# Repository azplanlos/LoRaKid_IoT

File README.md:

# LoRaKid

This is an IOT project to create hard and software for a kid's mobile phone like device but operation on LoRaWan over TTN.

CURRENTLY THIS IS WORK IN PROGRESS

## Image creation

Bitmaps can be created here: https://javl.github.io/image2cpp/

Settings are:

-

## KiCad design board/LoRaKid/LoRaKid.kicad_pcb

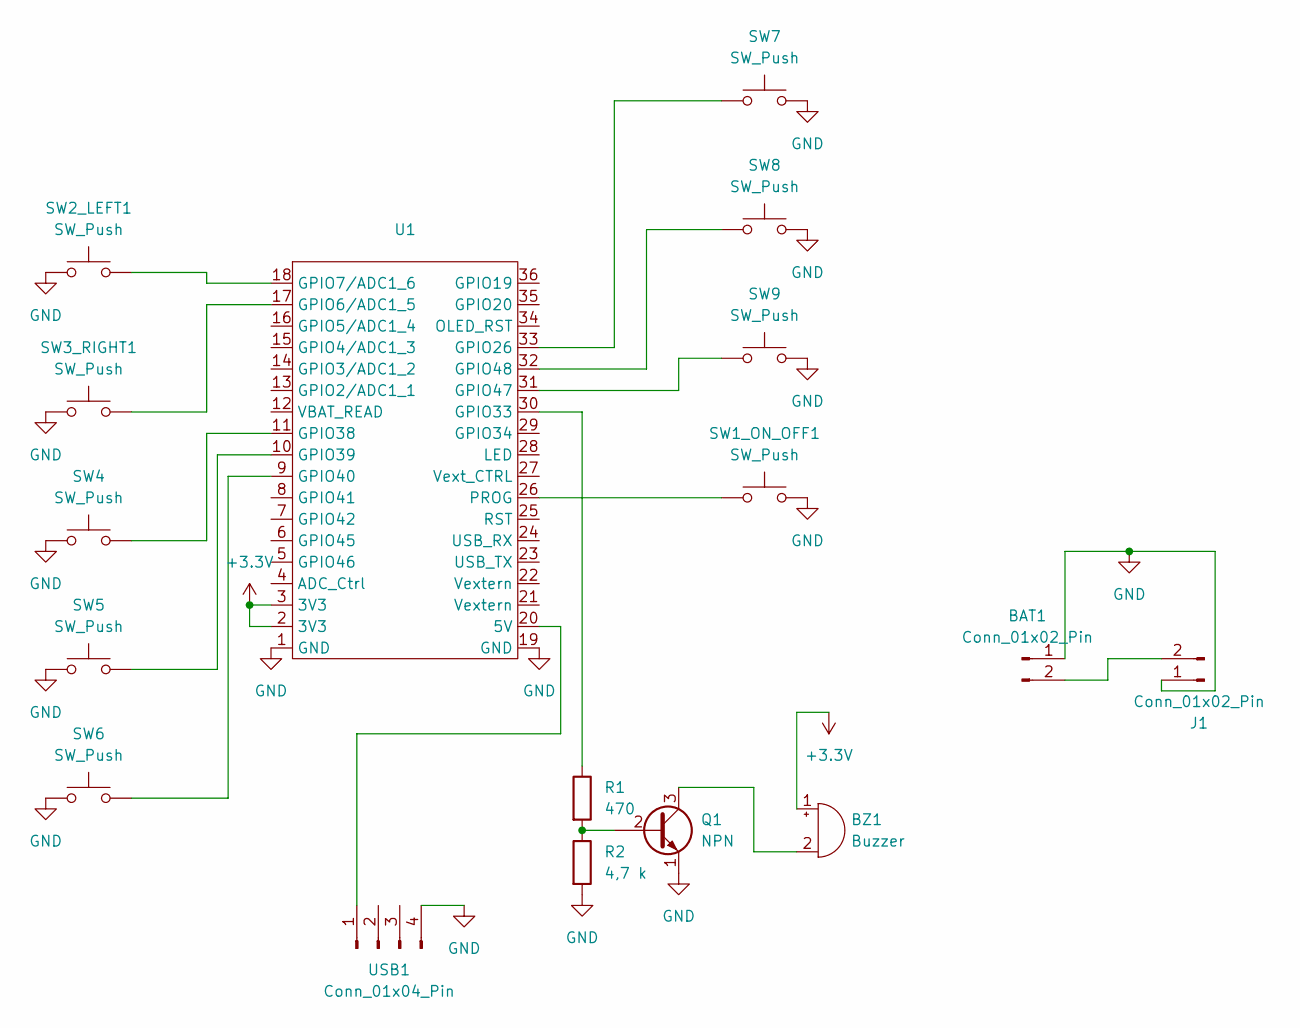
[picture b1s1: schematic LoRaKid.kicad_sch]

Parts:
BAT1: Conn_01x02_Pin; JST_PH_B2B-PH-K_1x02_P2.00mm_Vertical
BZ1: Buzzer; Buzzer_12x9.5RM7.6
J1: Conn_01x02_Pin; PinHeader_1x02_P2.54mm_Vertical
Q1: NPN; TO-92_Inline
R1: 470; R_0805_2012Metric_Pad1.20x1.40mm_HandSolder
R2: 4,7 k; R_0805_2012Metric_Pad1.20x1.40mm_HandSolder
SW1_ON_OFF1, SW2_LEFT1, SW3_RIGHT1, SW4, SW5, SW6, SW7, SW8, SW9: SW_Push; SW_SPST_Omron_B3FS-100xP
U1: Heltec LoRa 32 V3
USB1: Conn_01x04_Pin; PinSocket_1x04_P2.54mm_Vertical

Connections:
+3.3V: BZ1.1 (+), U1.2 (3V3), U1.3 (3V3)
GND: BAT1.1, J1.1, Q1.1 (E), R2.2, SW1_ON_OFF1.2, SW2_LEFT1.1, SW3_RIGHT1.1, SW4.1, SW5.1, SW6.1, SW7.2, SW8.2, SW9.2, U1.1 (GND), U1.19 (GND), USB1.4
unnamed: BAT1.2, J1.2
unnamed: BZ1.2 (-), Q1.3 (C)
unnamed: Q1.2 (B), R1.2, R2.1
unnamed: U1.20 (5V), USB1.1
unnamed: SW3_RIGHT1.2, U1.17 (GPIO6/ADC1_5)
unnamed: SW2_LEFT1.2, U1.18 (GPIO7/ADC1_6)
unnamed: SW7.1, U1.33 (GPIO26)
unnamed: R1.1, U1.30 (GPIO33)
unnamed: SW4.2, U1.11 (GPIO38)
unnamed: SW5.2, U1.10 (GPIO39)
unnamed: SW6.2, U1.9 (GPIO40)
unnamed: SW9.1, U1.31 (GPIO47)
unnamed: SW8.1, U1.32 (GPIO48)
unnamed: SW1_ON_OFF1.1, U1.26 (PROG)

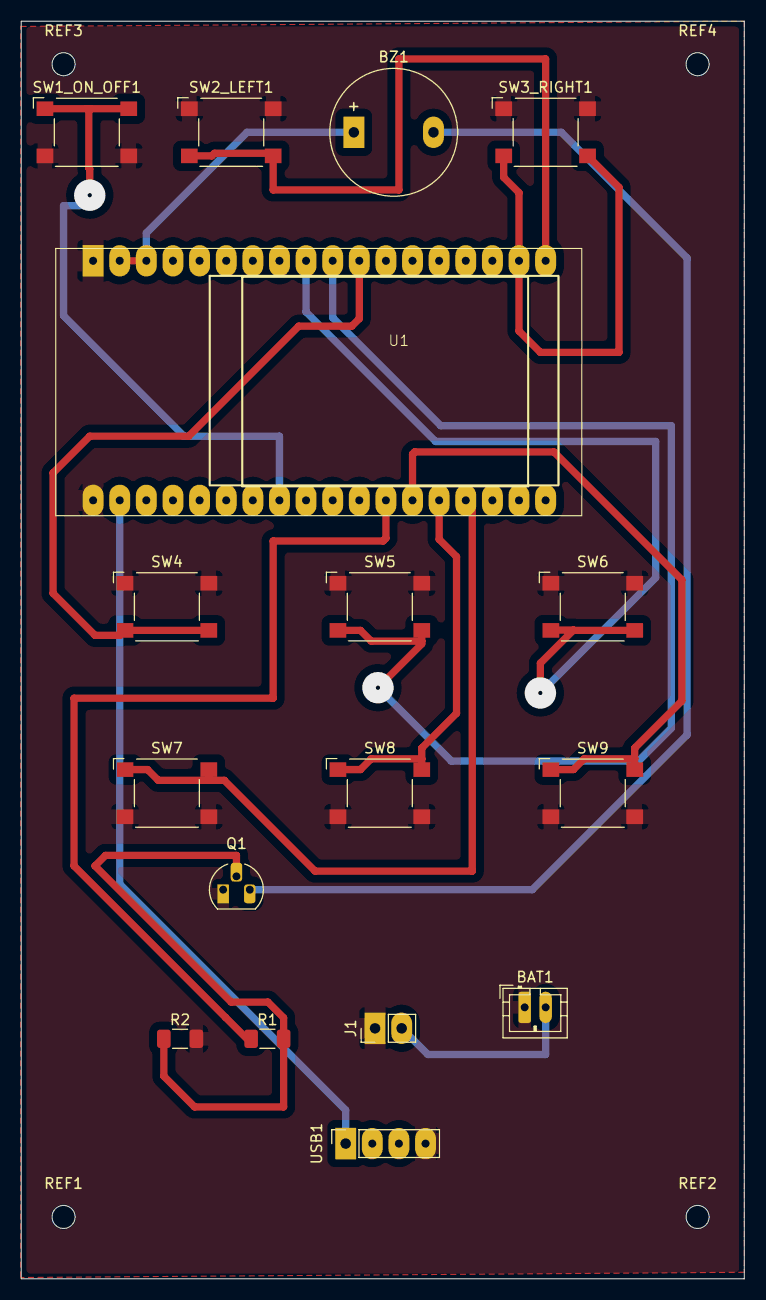
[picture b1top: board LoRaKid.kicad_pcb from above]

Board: 2 copper layers, 69.0 x 120.0 mm, 21 parts (0 on the bottom side), 16 nets.

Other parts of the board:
REF1, REF2, REF3, REF4: MountingHole_2.2mm_M2

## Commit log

2024-05-27 first lora draft
2024-05-27 sleep adjustmentd
2024-05-28 update firmware use protobuf
2024-05-28 add board schematics
2024-05-28 queue messages to send
2024-05-28 improve memory handling
2024-05-29 update board design
2024-05-29 fix gitignore
2024-05-29 update board layout
2024-05-29 add case
2024-07-05 update board layout and software
2024-07-06 heartbeat
2024-07-28 improvements on ui
2024-07-28 update protobuf
2024-10-19 melodie player
